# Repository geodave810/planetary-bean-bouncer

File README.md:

# Planetary Bean Bouncer

An open-source DIY coffee roaster built around an 8-cup stainless steel flour sifter, a planetary gear-driven agitator, and a stationary heat gun. The Planetary Bean Bouncer combines 3D-printed mechanical components, readily available hardware, and custom electronics to create an affordable small-batch coffee roasting platform.

> ⚠️ **Safety notice:** This project involves high temperatures, mains-powered equipment, and moving mechanical parts. Read `DISCLAIMER.md` before building or operating the roaster.

## Overview

The Planetary Bean Bouncer (PBB) is a small-batch coffee roaster designed around a modified stainless steel flour sifter. A planetary gear mechanism drives the agitator, continuously moving the beans while heat is applied by a stationary heat gun.

The project has evolved through several prototypes, with improvements to the mechanical assembly, electronics, firmware, and user interface.

There are currently two controller versions of the Planetary Bean Bouncer:

- **Arduino Version:** The original, lower-cost electronics design using an Arduino controller and a 1602 LCD display. This version remains fully functional and is a good choice for builders looking for a simpler and less expensive electronics package.
- **ESP32-S3 Version:** An updated controller featuring a custom-designed PCB, 4-inch TFT touchscreen, real-time clock, and SD card roast data logging. It provides a more advanced user interface and additional monitoring capabilities.

Both versions use the same basic roasting concept and mechanical platform. The ESP32-S3 version also incorporates several mechanical refinements.

This repository contains the firmware, hardware designs, 3D-printable parts, bill of materials, and documentation needed to build and experiment with the Planetary Bean Bouncer.

## Features

- Planetary gear-driven rotating agitator
- Stationary heat gun for bean heating
- Two controller options: Arduino and ESP32-S3
- Adjustable stepper motor speed
- Temperature monitoring using a K-type thermocouple
- Arduino version with 1602 LCD interface
- ESP32-S3 version with 4-inch TFT touchscreen
- DS3231 real-time clock on the ESP32-S3 version
- SD card roast data logging on the ESP32-S3 version
- Audible alerts and roast monitoring
- 3D-printed mechanical components

## Project Status

Both the Arduino and ESP32-S3 versions are functional.

The original Arduino version remains a reliable and less expensive option. The ESP32-S3 version represents the latest development, with updated electronics, a touchscreen interface, roast data logging, and several mechanical refinements.

The build guide, bill of materials, and controller documentation are being maintained as the project continues to develop.

## Repository Contents

The repository contains the following main sections:

- `firmware/` — Controller firmware for the supported versions.
- `hardware/` — Mechanical designs, STL files, and hardware reference information.
- `wiring/` — Wiring references and diagrams.
- `docs/` — Build guides, bill of materials, FAQ, and other documentation.
- `PBB_ESP32_S3/` — Updated ESP32-S3 controller design files and associated resources.
- `media/` — Project photographs and videos.

The original hardware directory retains the earlier mechanical designs, including the fully 3D-printed planetary gearbox. The ESP32-S3 directory contains the updated mechanical parts and electronics designs.

Refer to the current build guide and BOM when selecting parts for the ESP32-S3 version.

## Mechanical Design Updates

Several mechanical changes were made as the design evolved.

### Agitator Shaft

The original design used a 5 mm shaft. The stainless steel 3D-printed wobble disc was subsequently drilled out to 6 mm, and this larger shaft has been holding well under the operating load.

The updated 3D-printed shaft design, with a 6.5 mm clearance hole, is included in the ESP32-S3 directory.

### Planetary Gearbox

The original design used a completely 3D-printed planetary gearbox. This design remains available in the original hardware directory for builders who prefer to print their own gearbox.

The ESP32-S3 version uses a commercially manufactured planetary gear assembly. This reduces the number of printed parts considerably and simplifies construction.

Both approaches are valid, and builders can choose the arrangement that best suits their needs.

## Hardware Overview

The Planetary Bean Bouncer uses a modified 8-cup stainless steel flour sifter, a planetary gear mechanism, a NEMA 17 stepper motor, and a stationary consumer heat gun.

The electronics depend on the controller version selected.

### Arduino Version

- Arduino Uno or compatible controller
- Stepper motor driver, such as DRV8825 or TMC2209
- NEMA 17 stepper motor
- MAX6675 thermocouple interface
- 1602 LCD display
- Push-button controls

This version provides the basic motor control and temperature monitoring functions at a lower electronics cost.

### ESP32-S3 Version

- ESP32-S3 development module
- Custom-designed controller PCB
- 4-inch TFT touchscreen
- Integrated stepper motor driver circuitry
- MAX6675 thermocouple interface
- DS3231 real-time clock
- SD card storage
- Audible alerts

### Alternative ESP32-S3 Development Board

The custom ESP32-S3 controller PCB is not required to build the ESP32-S3 version. During development, I also used an inexpensive 44-pin ESP32-S3 N16R8 development board with a GPIO expansion board.

This provides an alternative for builders who prefer a prototype-style electronics assembly rather than manufacturing the custom controller PCB.

The N16R8 version provides 16 MB flash and 8 MB PSRAM. Boards are available with either an onboard antenna or an external antenna connector.

**Important compatibility note:** If you plan to install an ESP32-S3 development board directly onto the custom controller PCB, check the spacing between the two rows of header pins before purchasing. The custom PCB accommodates two pin-spacing options: 0.9 inches and 1.0 inches. Some development boards use 1.1-inch spacing and will not fit.

Using a separate GPIO expansion board, like the one included with my prototype, avoids this physical spacing limitation.

These development boards are available from multiple sellers and may have hardware revisions or differences in their power circuitry. My prototype required a solder-pad modification to provide 5V at the board's 5V connection, and occasionally required a second boot attempt. Verify the board's power connections and operation before incorporating it into the roaster.

Follow the ESP32-S3 wiring diagram for GPIO assignments and peripheral connections. Not every development board will have identical hardware.

Refer to the corresponding build documentation and bill of materials for component details, wiring, and assembly information.

## Build Guide and Bill of Materials

Build documentation and a bill of materials are provided in the `docs/` directory.

The build guide covers mechanical construction, electronics, wiring, and controller setup. The BOM identifies the components and hardware needed for the build.

Make sure to use the documentation corresponding to the controller version you intend to build.

## Fit & Tolerance Test Prints

Two optional test STLs are included to verify printer tolerances before printing the main components:

- **`hardware/STL/accessories/Test_1.stl`** – Verifies screw, nut, bearing, and lever-lock electrical terminal fits.
- **`hardware/STL/accessories/Gearing_5_1_16_24_64_Test_Rev36.stl`** – A reduced-size planetary gear set using the same tolerances as the full 3D-printed gearbox. It can also be used as a fidget.

These test prints are highly recommended if your printer or filament has not been tested with the design.

See `docs/tolerance-test-prints.md` for additional details.

## Quick Start

Before building:

1. Read `DISCLAIMER.md` and the project FAQ.
2. Decide whether you want to build the Arduino or ESP32-S3 version.
3. Review the appropriate build guide and bill of materials.
4. Review the corresponding hardware and STL directories.
5. Obtain and assemble the required mechanical and electronic components.
6. Follow the firmware instructions for your selected controller.
7. Test motor operation, temperature monitoring, and controller functions without applying heat.
8. Complete the assembly and perform appropriate safety checks before roasting.

## ESP32-S3 PCB Design and Gerber Files

The repository includes the KiCad project files and Gerber files for the custom ESP32-S3 controller board.

The supplied Gerber files retain the decorative back silkscreen image used on the manufactured board. The image was intentionally removed from the published KiCad source files to reduce file size and avoid image-clipping warnings.

Builders can use the supplied Gerbers to manufacture the board as designed, or modify the KiCad project and generate their own Gerbers.

## Licensing

This project uses multiple licenses:

- **Firmware:** MIT License
- **Hardware design files (STL, images, diagrams):** Creative Commons Attribution-NonCommercial 4.0 International (CC BY-NC 4.0)

The hardware license allows free personal and educational use while restricting commercial use without permission.

See the individual license files for details.

## Support This Project ☕

This project is released as open source and free to use.

If you find it useful and would like to support continued development, documentation, and future improvements, you can:

☕ **Buy me a coffee:** https://buymeacoffee.com/geodave

Support is entirely optional, but always appreciated.

## Credits

Project design and implementation: **David Bunch**

Firmware was developed with AI-assisted code generation and subsequently reviewed, tested, and maintained by the author.

Some components and design elements are derived from existing open-source projects and are credited in the relevant subdirectories.

## Build Log and Videos

The Planetary Bean Bouncer has been developed and documented over time through videos and a long-running build discussion.

### YouTube Playlist

A playlist documenting the design, prototyping, testing, and development of the Planetary Bean Bouncer:

https://www.youtube.com/playlist?list=PLyy5iFdDEfauqgzqg_eptvup8FIkFzkNk

New videos may be added as the project continues to evolve.

### Build Log

A detailed build log and discussion thread dating back to September 2025, including design decisions, experiments, and lessons learned:

https://forum.v1e.com/t/diy-coffee-roaster/51195

These resources provide additional background and context beyond what is included in the repository.

## FAQ

Common questions about build difficulty, food safety, and project scope are answered here:

➡️ [docs/FAQ.md](docs/FAQ.md)

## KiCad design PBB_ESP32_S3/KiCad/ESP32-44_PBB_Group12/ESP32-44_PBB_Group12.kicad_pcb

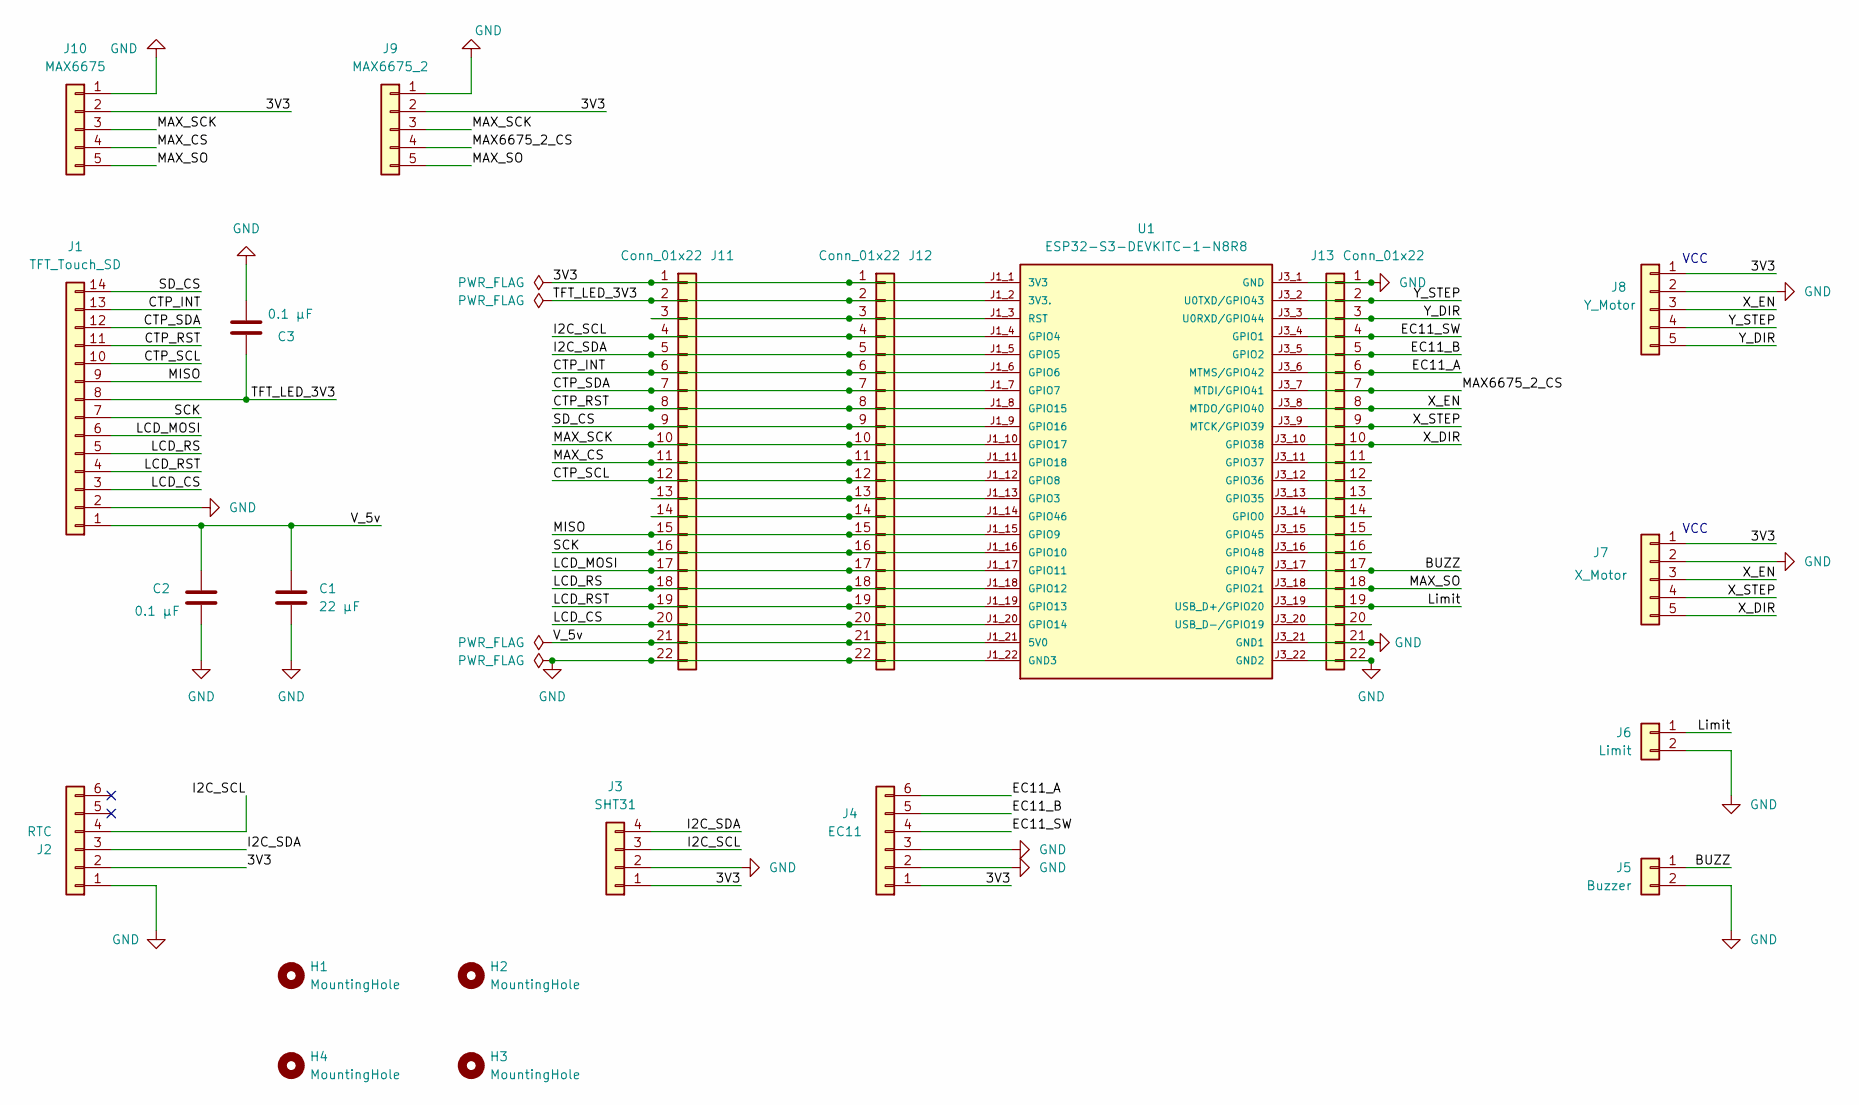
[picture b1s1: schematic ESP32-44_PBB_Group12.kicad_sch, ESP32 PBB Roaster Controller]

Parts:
C1: 22 µF; C_1210_3225Metric
C2, C3: 0.1 µF; C_1206_3216Metric
H1, H2, H3, H4: MountingHole; MountingHole_3.2mm_M3
J1: TFT_Touch_SD; PinSocket_1x14_P2.54mm_Vertical
J2: RTC; PinSocket_1x06_P2.54mm_Vertical
J3: SHT31; PinSocket_1x04_P2.54mm_Vertical
J4: EC11; PinSocket_1x06_P2.54mm_Vertical
J5: Buzzer; PinHeader_1x02_P2.54mm_Vertical
J6: Limit; PinHeader_1x02_P2.54mm_Vertical
J7: X_Motor; PinHeader_1x05_P2.54mm_Vertical
J8: Y_Motor; PinHeader_1x05_P2.54mm_Vertical
J9: MAX6675_2; PinSocket_1x05_P2.54mm_Horizontal_Mirrored
J10: MAX6675; PinSocket_1x05_P2.54mm_Horizontal_Mirrored
J11, J13: Conn_01x22; PinHeader_1x22_P2.54mm_Vertical
J12: Conn_01x22; ESP32_22_PadsOnly
U1: ESP32-S3-DEVKITC-1-N8R8

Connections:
/3V3: J2.2, J3.1, J4.1, J7.1, J8.1, J9.2, J10.2, J11.1, J12.1, U1.J1_1 (3V3)
/BUZZ: J5.1, J13.17, U1.J3_17 (GPIO47)
/CTP_INT: J1.13, J11.6, J12.6, U1.J1_6 (GPIO6)
/CTP_RST: J1.11, J11.8, J12.8, U1.J1_8 (GPIO15)
/CTP_SCL: J1.10, J11.12, J12.12, U1.J1_12 (GPIO8)
/CTP_SDA: J1.12, J11.7, J12.7, U1.J1_7 (GPIO7)
/EC11_A: J4.6, J13.6, U1.J3_6 (MTMS/GPIO42)
/EC11_B: J4.5, J13.5, U1.J3_5 (GPIO2)
/EC11_SW: J4.4, J13.4, U1.J3_4 (GPIO1)
/I2C_SCL: J2.4, J3.3, J11.4, J12.4, U1.J1_4 (GPIO4)
/I2C_SDA: J2.3, J3.4, J11.5, J12.5, U1.J1_5 (GPIO5)
/LCD_CS: J1.3, J11.20, J12.20, U1.J1_20 (GPIO14)
/LCD_MOSI: J1.6, J11.17, J12.17, U1.J1_17 (GPIO11)
/LCD_RS: J1.5, J11.18, J12.18, U1.J1_18 (GPIO12)
/LCD_RST: J1.4, J11.19, J12.19, U1.J1_19 (GPIO13)
/Limit: J6.1, J13.19, U1.J3_19 (USB_D+/GPIO20)
/MAX6675_2_CS: J9.4, J13.7, U1.J3_7 (MTDI/GPIO41)
/MAX_CS: J10.4, J11.11, J12.11, U1.J1_11 (GPIO18)
/MAX_SCK: J9.3, J10.3, J11.10, J12.10, U1.J1_10 (GPIO17)
/MAX_SO: J9.5, J10.5, J13.18, U1.J3_18 (GPIO21)
/MISO: J1.9, J11.15, J12.15, U1.J1_15 (GPIO9)
/SCK: J1.7, J11.16, J12.16, U1.J1_16 (GPIO10)
/SD_CS: J1.14, J11.9, J12.9, U1.J1_9 (GPIO16)
/TFT_LED_3V3: C3.1, J1.8, J11.2, J12.2, U1.J1_2 (3V3.)
/V_5v: C1.1, C2.1, J1.1, J11.21, J12.21, U1.J1_21 (5V0)
/X_DIR: J7.5, J13.10, U1.J3_10 (GPIO38)
/X_EN: J7.3, J8.3, J13.8, U1.J3_8 (MTDO/GPIO40)
/X_STEP: J7.4, J13.9, U1.J3_9 (MTCK/GPIO39)
/Y_DIR: J8.5, J13.3, U1.J3_3 (U0RXD/GPIO44)
/Y_STEP: J8.4, J13.2, U1.J3_2 (U0TXD/GPIO43)
GND: C1.2, C2.2, C3.2, J1.2, J2.1, J3.2, J4.2, J4.3, J5.2, J6.2, J7.2, J8.2, J9.1, J10.1, J11.22, J12.22, J13.1, J13.21, J13.22, U1.J1_22 (GND3), U1.J3_1 (GND), U1.J3_21 (GND1), U1.J3_22 (GND2)
unnamed: J11.3, J12.3, U1.J1_3 (RST)
unnamed: J11.13, J12.13, U1.J1_13 (GPIO3)
unnamed: J11.14, J12.14, U1.J1_14 (GPIO46)
unnamed: J13.11, U1.J3_11 (GPIO37)
unnamed: J13.12, U1.J3_12 (GPIO36)
unnamed: J13.13, U1.J3_13 (GPIO35)
unnamed: J13.14, U1.J3_14 (GPIO0)
unnamed: J13.15, U1.J3_15 (GPIO45)
unnamed: J13.16, U1.J3_16 (GPIO48)
unnamed: J13.20, U1.J3_20 (USB_D-/GPIO19)

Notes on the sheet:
VCC

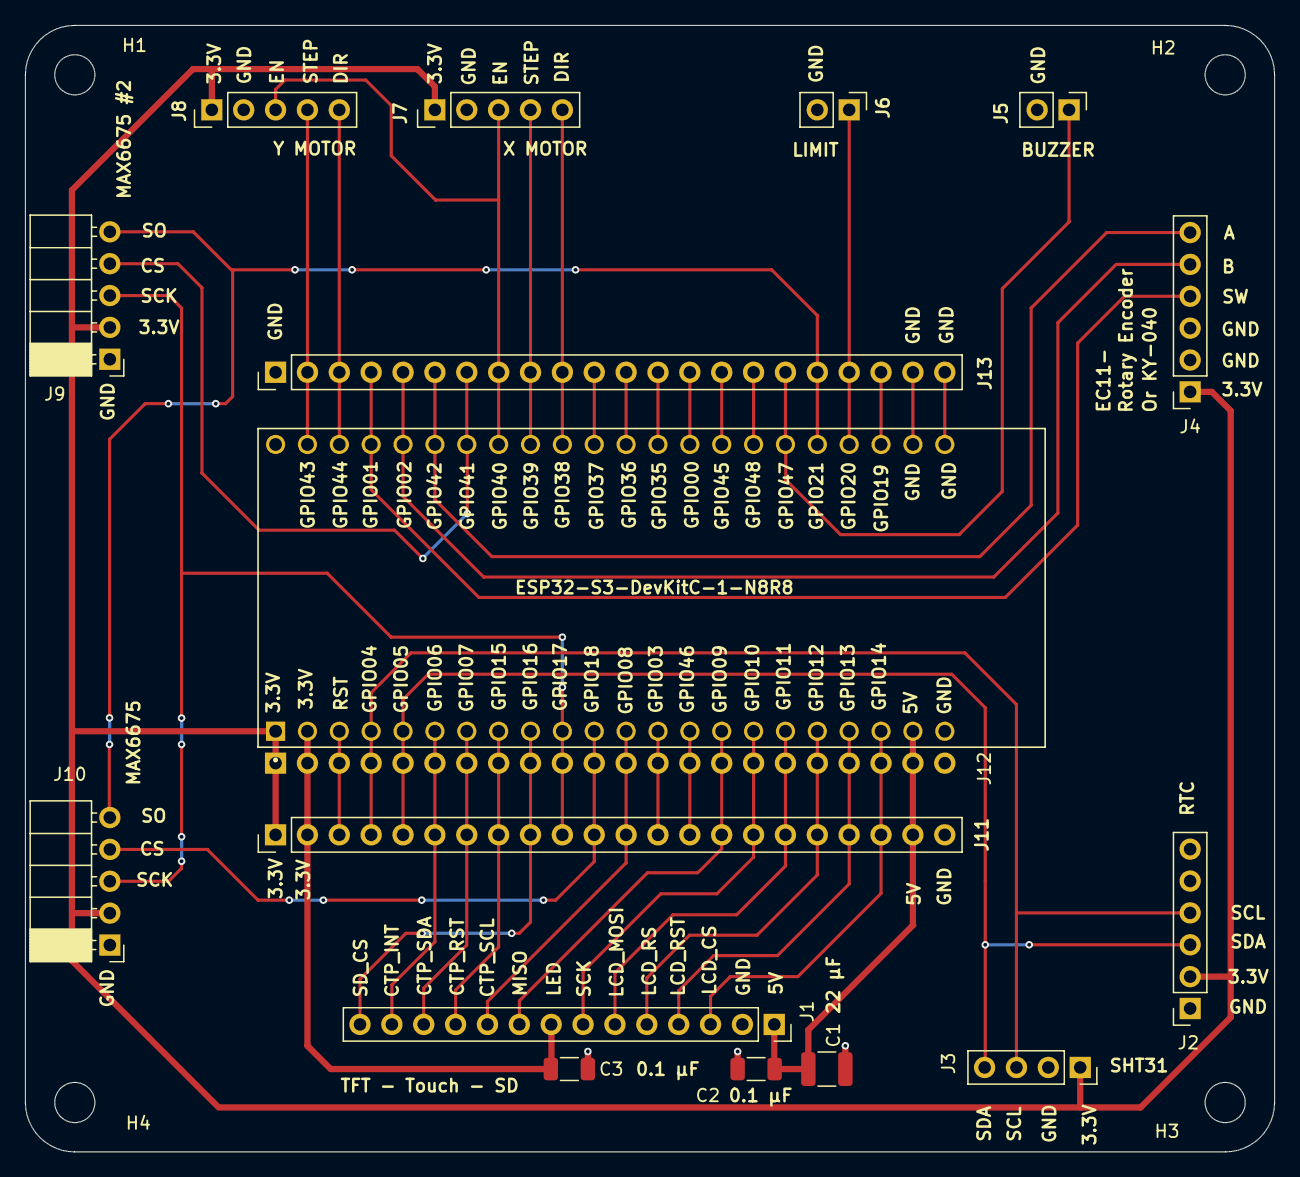
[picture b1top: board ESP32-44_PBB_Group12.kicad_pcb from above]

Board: 2 copper layers, 99.6 x 89.8 mm, 21 parts (0 on the bottom side), 41 nets.

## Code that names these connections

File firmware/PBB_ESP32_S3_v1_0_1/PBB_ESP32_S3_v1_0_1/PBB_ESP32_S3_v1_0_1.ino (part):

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// MOSI 13, MISO 15, SCLK 14, CS 10, DC 12, RST 11

// FT6336 capacitive touch
#define CTP_SDA   7
#define CTP_SCL   8
#define CTP_RST   15
#define CTP_INT   6
#define FT6336_ADDR 0x38

// SD card shares TFT SPI bus
#define SD_CS 16

// Physical TFT reset pin (matches TFT_eSPI setup).
#define PBB_TFT_RST 13
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  motorEnabled = false;

  pinMode(TFT_CS, OUTPUT);
  pinMode(SD_CS, OUTPUT);
  digitalWrite(TFT_CS, HIGH);
  digitalWrite(SD_CS, HIGH);

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
  // Touch - same initialization as working touch test
  Serial.println("Initializing touch...");
  pinMode(CTP_RST, OUTPUT);
  digitalWrite(CTP_RST, LOW);
  delay(20);
  digitalWrite(CTP_RST, HIGH);
  delay(300);

  pinMode(CTP_INT, INPUT);
  Wire.begin(CTP_SDA, CTP_SCL);
  Wire.setClock(100000);
  Serial.println("TOUCH PASSED");
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
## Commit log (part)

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2026-01-17 Add mechanical build guide and correct BOM omissions
2026-01-17 Create README.md
    Added docs/README.md
2026-01-17 Minor edits to build guide
2026-01-18 Updated drill guide STL file and BOM
2026-01-18 Updated Cover Image
2026-01-26 Small changes to tidy of electrical
2026-01-26 FAQ create and minor changes to 2 README.md files
2026-01-26 Correction to Arduiono Base Mount
2026-01-26 Update arduino Uno Base
2026-01-28 Updated Build guide and some STL files
2026-01-28 Changed Cover Image
2026-01-28 adjust cover image
2026-01-28 Added Test print image
2026-01-28 Adjusted README and buildguide
2026-01-29 Minor Changes before release
2026-01-29 Minor changes to build guide
